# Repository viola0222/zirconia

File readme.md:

## 概要
___

「zirconia v.2.0」はマイクロマウスのチャンピオンが製作したオープンソースのマイクロマウスをnakagawaが改訂した版です。
 
詳しい説明は、[こちらのリンクの資料](https://docs.google.com/presentation/d/1BjXeR3dtw2jEZHByvPkCKbgB9d2WKhvbEWPhUpI-utg/edit?usp=sharing)を参照してください。

## 機能
___
 
各種インターフェースやセンサーの動作確認  

- マイコン各種機能(STM32F411)
- LED
- プッシュスイッチ
- モータ
- エンコーダ(MA730)
- IMU(ICM-42688-P)
- IRセンサ
  
機能の詳細についてはソフトマニュアルとサンプルコードのindex.hを参照して下さい。
 
## 動作環境
___
 
- 統合開発環境
    - STM32CubeIDE
    - Version :  1.15.0
    - URL : https://www.st.com/ja/development-tools/stm32cubeide.html
    - STM32CubeMX
    - Version :  6.10.0
    - URL : https://www.st.com/ja/development-tools/stm32cubemx.html    

- フラッシュライター
	- STM32CubeProgrammer
	- Version : 2.16.0
 	- URL : https://www.st.com/ja/development-tools/stm32cubeprog.html

※ Versionにはサンプルプログラムを開発したときのものを記載してあります。  
　　基本的には最新版をインストールすべきだと思いますが、  
　　サンプルプログラムが動かない等の不具合がありましたら参考にして下さい。

## 構成
___
 
- hardware
    - 回路図やガーバーデータ、部品リストなどハードウェアデータ
    - STEP 3D View https://a360.co/4cjsH3n
    
- software
    - CubeMXで自動生成したソフトと本サンプルプログラム
    - Incフォルダ内のIndex.hにサンプルプログラムの使い方が記載されています
    - Srcフォルダ内にmain.cなどのサンプルプログラムが入っています
- ハードマニュアル
    - ハードウェアの作り方や構成について記載されています
- ソフトマニュアル
    - サンプルプログラムの導入や使い方について記載されていますS
 
## その他
 ___

__本サンプルコードではマイクロマウスとして迷路を完走させることはできません。__  
本サンプルコードの目的は、製作したハードウェアの動作確認であり、その副産物として、マイクロマウスとして使いやすいデバイスドライバが書かれています。  
  
あくまでもzirconiaは動くハードウェアを用意しただけなので、ソフトウェアは自力で頑張れる人向けです。電子工作やプログラミングのガチ初心者にはオススメしません。  
電子工作や組み込みプログラム入門として、マイクロマウスを始める場合には(株)アールティより販売されている学習キット[Pi:Co Classic3.4 ESP32-S3](https://rt-net.jp/products/pico-classic3-esp32)や[Pi:Co V2](https://rt-net.jp/products/pico-v2)がオススメです。
 
## 作者
___
 
[Noriaki Nakagawa](https://github.com/noriakinakagawa)  
zirconia_sample is licensed under the Apache License, Version2.0

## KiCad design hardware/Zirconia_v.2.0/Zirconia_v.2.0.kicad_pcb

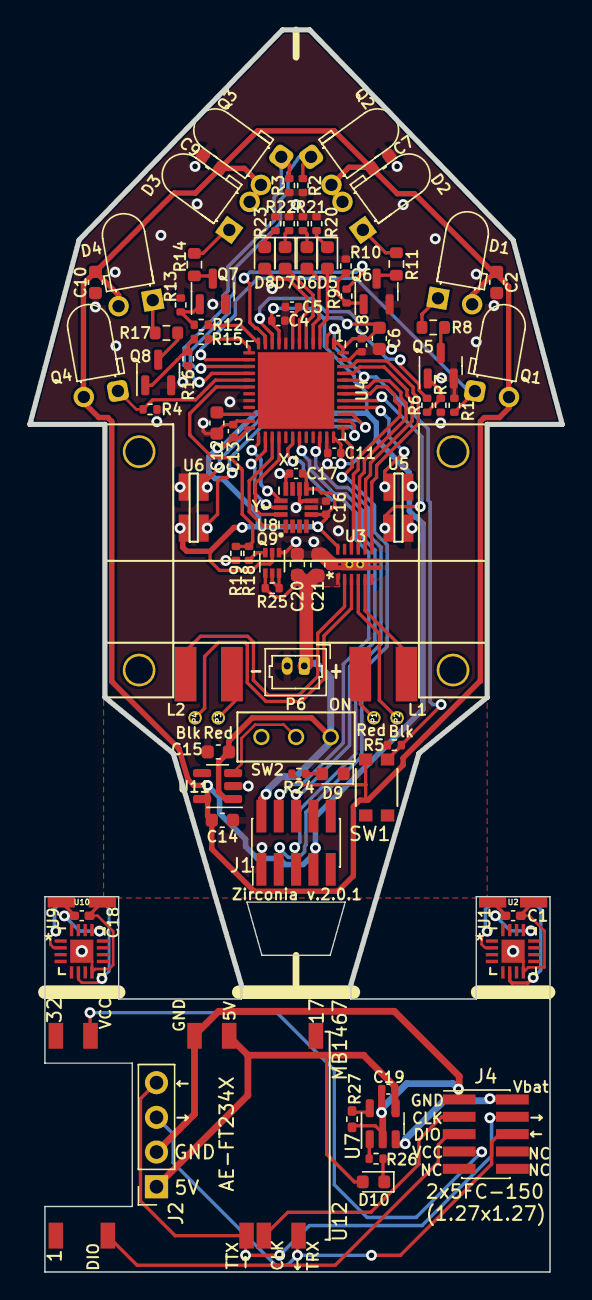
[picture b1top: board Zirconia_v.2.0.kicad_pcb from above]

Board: 2 copper layers, 39.0 x 90.9 mm, 91 parts (0 on the bottom side), 80 nets.

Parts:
C1, C18: 0.1u; C_0402_1005Metric_Pad0.74x0.62mm_HandSolder
C2, C6, C7, C9, C10, C12, C14, C15, C20, C21: 10u; C_0603_1608Metric
C4, C5, C8, C11, C13, C16: 0.1u; C_0402_1005Metric
C17: 10n; C_0402_1005Metric
C19: 4.7u; C_0402_1005Metric
D1, D3: OSI5FU3A11C
D2, D4: OSI5FU3A11C; OSI5FU3A11C_Reverse
D5: XL-1608UYC-06; LED_0603_1608Metric
D6, D10: XL-1608SURC-06; LED_0603_1608Metric
D7: XL-1608SYGC-06; LED_0603_1608Metric
D8, D9: XL-1608UBC-04; LED_0603_1608Metric
J1, J4: BD125-10-A-0305-0580-L-B; PinHeader_2x05_P1.27mm_Vertical_SMD
J2: Conn_01x04; PinSocket_1x04_P2.54mm_Vertical
L1, L2: 47uH; Inductor
Mot_mount: V; Mot_mount
P1, P3: Red; motor_pin
P2, P4: Blk; motor_pin
P6: PicoBlade_53047-0210; Molex_PicoBlade_53047-0210_1x02_P1.25mm_Vertical
Q1, Q2: LTR; Phototransistor_D3.0mm_Horizontal_O1.27mm_Z2.0mm_IRBlack
Q3, Q4: LTR; Phototransistor_D3.0mm_Horizontal_O1.27mm_Z2.0mm_IRBlack_Re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
Q5, Q6, Q7, Q8: IRLML6344; SOT-23
Q9: DMC2400UV-7; SOT-563
R1, R2, R3, R4, R6, R9, R12, R15, R20, R21, R23, R24, R26: 1k; R_0402_1005Metric
R5, R18, R19, R25: 10k; R_0402_1005Metric
R7, R10, R13, R16: 100k; R_0402_1005Metric
R8, R11, R14, R17: 10; R_0603_1608Metric
R22: 510; R_0402_1005Metric
R27: 10k; R_0402_1005Metric_Pad0.72x0.64mm_HandSolder
SW1: KMR211NG LFS; KMR2xxNG_LFS
SW2: SS12D01G4
U1, U9: MA302/MA730; MA302GQ-P
U2, U10: ENCODER_CONNECT_IC; ENC_CONN_VART
U3: DRV8836DSSR
U4: STM32F411CEU6/STM32F413CHU6; QFN-48-1EP_7x7mm_P0.5mm_EP5.6x5.6mm
U5, U6: ENCODER_CONNECT_PCB; ENC_CONN_FLAT
U7: MCP73831T-2ACI/OT; SOT-23-5
U8: ICM-42688-P; ICM-42688-P_handsoldering
U11: LP5907MFX-3.0; SOT-23-5
U12: STLINK-V3MOS; mod_stlink-v3m_mb1467

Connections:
+3V0: C2.1, C4.1, C6.1, C7.1, C8.1, C9.1, C10.1, C11.1, C13.1, C14.1, C16.1, C17.1, D1.2 (A), D2.2 (A), D3.2 (A), D4.2 (A), J1.7, Q1.2 (C), Q2.2 (C), Q3.2 (C), Q4.2 (C), Q9.2 (G), R24.2, SW1.2, U3.12 (NSLEEP), U4.1 (VBAT), U4.9 (VDDA/VREF+), U4.24 (VDD), U4.36 (VDD), U4.48 (VDD), U5.1 (VCC), U6.1 (VCC), U8.5 (VDDIO), U8.8 (VDD), U11.5 (OUT)
+BATT: C15.1, C20.1, C21.1, J1.2, P6.1, Q9.4 (S), R25.1, SW2.1 (A), U3.1 (VCC), U11.1 (IN)
GND: C2.2, C4.2, C5.2, C6.2, C7.2, C8.2, C9.2, C10.2, C11.2, C12.2, C13.2, C14.2, C15.2, C16.2, C17.2, C20.2, C21.2, D9.1 (K), J1.1, P6.2, Q5.2 (S), Q6.2 (S), Q7.2 (S), Q8.2 (S), Q9.1 (S), R1.2, R2.2, R3.2, R4.2, R5.2, R7.2, R10.2, R13.2, R16.2, R19.2, R20.1, R21.1, R22.1, R23.1, U3.6 (GND), U3.13 (EPAD), U4.8 (VSSA/VREF-), U4.20 (PB2/BOOT1), U4.23 (VSS), U4.35 (VSS), U4.47 (VSS), U5.2 (GND), U6.2 (GND), U8.6 (GND), U8.7 (RESV_7), U8.9 (INT2/FSYNC/CLKIN), U8.11 (RESV_11), U11.2 (GND)
unnamed: D1.1 (K), R8.1
unnamed: D2.1 (K), R11.1
unnamed: D3.1 (K), R14.1
unnamed: D4.1 (K), R17.1
unnamed: D5.2 (A), U4.3 (PC14/OSC32-IN)
unnamed: D5.1 (K), R20.2
unnamed: D6.2 (A), U4.4 (PC15/OSC32-OUT)
unnamed: D6.1 (K), R21.2
unnamed: D7.2 (A), U4.5 (PH0/OSC-IN)
unnamed: D7.1 (K), R22.2
unnamed: D8.2 (A), U4.6 (PH1/OSC-OUT)
unnamed: D8.1 (K), R23.2
unnamed: D9.2 (A), R24.1
unnamed: C19.1, D10.2 (A), J2.1, U7.4 (V_{DD}), U12.22 (5V_OPT)
unnamed: D10.1 (K), R26.2
unnamed: J1.3, U4.37 (PA14/SWCLK)
unnamed: J1.4, U4.30 (PA9/USART1TX)
unnamed: J1.5, U4.34 (PA13/SWDIO)
unnamed: J1.6, U4.31 (PA10/USRAT1RX)
unnamed: C19.2, J2.2, J4.1, R27.2, U7.2 (V_{SS}), U12.24 (GND)
unnamed: J2.3, J4.6, U12.15 (T_VCP_RX)
unnamed: J2.4, J4.4, U12.12 (T_VCP_TX)
unnamed: J4.2, U7.3 (V_{BAT})
unnamed: J4.3, U12.13 (T_JCLK/T_SWCLK)
unnamed: J4.5, U12.4 (T_JTMS/T_SWDIO)
unnamed: J4.7, U12.30 (T_VCC)
unnamed: L1.1, P1.1
unnamed: L2.1, P3.1
unnamed: Q1.1 (E), R1.1, U4.14 (PA4/ADC1-4)
unnamed: Q2.1 (E), R2.1, U4.15 (PA5/TIM2-1/SPI1SCK/ADC1-5)
unnamed: Q3.1 (E), R3.1, U4.16 (PA6/TIM3-1/SPI1MISO/ADC1-6)
unnamed: Q4.1 (E), R4.1, U4.17 (PA7/TIM3-2/SPI1MOSI/ADC1-7)
unnamed: Q5.3 (D), R8.2
unnamed: Q5.1 (G), R6.2, R7.1
unnamed: Q6.3 (D), R11.2
unnamed: Q6.1 (G), R9.2, R10.1
unnamed: Q7.3 (D), R14.2
unnamed: Q7.1 (G), R12.2, R13.1
unnamed: Q8.3 (D), R17.2
unnamed: Q8.1 (G), R15.2, R16.1
unnamed: Q9.5 (G), Q9.6 (D), R25.2
unnamed: Q9.3 (D), R18.1
unnamed: SW2.2 (B), U11.3 (EN)
unnamed: U1.2 (A), U2.3 (A)
unnamed: U1.6 (B), U2.4 (B)
unnamed: C1.1, U1.8 (GND), U1.17 (PAD), U2.2 (GND)
unnamed: C1.2, U1.13 (VDD), U2.1 (VCC)
unnamed: U3.10 (AIN1/APHASE), U4.42 (PB6/TIM4-1)
unnamed: U3.9 (AIN2/AENBL), U4.43 (PB7/TIM4-2)
unnamed: L2.2, U3.2 (AOUT1)
unnamed: P4.1, U3.3 (AOUT2)
unnamed: U3.8 (BIN1/BPHASE), U4.45 (PB8/TIM4-3)
unnamed: U3.7 (BIN2/BENBL), U4.46 (PB9/TIM4-4)
unnamed: P2.1, U3.4 (BOUT1)
unnamed: L1.2, U3.5 (BOUT2)
unnamed: R5.1, SW1.1, U4.2 (PC13), U4.44 (BOOT0)
unnamed: C5.1, U4.7 (NRST)
unnamed: R6.1, U4.10 (PA0/TIM2-1,5-1/ADC1-0)
unnamed: R9.1, U4.11 (PA1/TIM2-2,5-2/ADC1-1)
unnamed: R12.1, U4.12 (PA2/TIM2-3,5-3/ADC1-2)
unnamed: R15.1, U4.13 (PA3/TIM2-4,5-4/ADC1-3)
unnamed: U4.38 (PA15/TIM2-1), U6.3 (A)
unnamed: R18.2, R19.1, U4.18 (PB0/TIM3-3/ADC1-8)
unnamed: U4.39 (PB3/TIM2-2/SPI1SCK/SPI3SCK), U6.4 (B)
unnamed: U4.40 (PB4/TIM3-1/SPI1MISO/SPI3MISO), U5.3 (A)
unnamed: U4.41 (PB5/TIM3-2/SPI1MOSI/SPI3MOSI), U5.4 (B)
unnamed: U4.25 (PB12/SPI3SCK), U8.12 (AP_CS)
unnamed: U4.26 (PB13/SPI2SCK), U8.13 (AP_SCL/AP_SCLK)
unnamed: U4.27 (PB14/SPI2MISO), U8.1 (AP_SDO/AP_AD0)
unnamed: U4.28 (PB15/SPI2MOSI), U8.14 (AP_SDA/AP_SDIO/AP_SDI)
unnamed: C12.1, U4.22 (VCAP1)
unnamed: R27.1, U7.5 (PROG)
unnamed: R26.1, U7.1 (STAT)
unnamed: U9.2 (A), U10.3 (A)
unnamed: U9.6 (B), U10.4 (B)
unnamed: C18.1, U9.8 (GND), U9.17 (PAD), U10.2 (GND)
unnamed: C18.2, U9.13 (VDD), U10.1 (VCC)

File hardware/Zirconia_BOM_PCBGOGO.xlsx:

品名（Name） | 部品番号（Designator） | 個数（Quantity） | 値（Value） | パッケージ（Package） | 説明（Description） | 部品メーカー（Manufacturer） | 部品メーカーの型番（Manufacturer Part Number） | 代替可否だいたいかひ | Link
セラミックコンデンサ | C1,C4,C5,C8,C11,C13,C16,C17,C18,C19 | 10 | 0.1uF 16V | 表面実装1608mmひょうめんじっそう |  | Samsung | CL10B104KO8NNNC | 可か | https://www.digikey.jp/product-detail/ja/samsung-electro-mec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
セラミックコンデンサ | C2,C6,C7,C9,C10,C12,C14,C15 | 8 | 10uF 10V | 表面実装1608mmひょうめんじっそう |  | Samsung | CL10A106MP8NNNC | 可か | https://www.digikey.jp/product-detail/ja/samsung-electro-mec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
セラミックコンデンサ | C3 | 1 | 47uF 6.3V | 表面実装3216mmひょうめんじっそう |  | Samsung | CL31A476MQHNNWE | 可か | https://www.digikey.jp/product-detail/ja/samsung-electro-mec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
ＩＣ | U3 | 1 |  | 12-WFDFN | 向きがあるので、実装注意 (本ファイル別タブ「部品実装向き」参照)むじっそうちゅういほんべつﾌﾞﾋﾝｼﾞｯｿｳﾑさんしょう | Texas Instruments | DRV8836DSSR | 不可ふか | https://www.digikey.jp/product-detail/ja/texas-instruments/D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
インダクタ | L1,L2 | 2 | 47uH | 表面実装4.00mm x 4.00mmひょうめんじっそう |  | Vishay Dale | IFSC1515AHER470M01 | 不可ふか | https://www.digikey.jp/product-detail/ja/vishay-dale/IFSC151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
ＬＥＤ | D5 | 1 |  | 表面実装1608mmひょうめんじっそう | 向きがあるので、実装注意 (本ファイル別タブ「部品実装向き」参照)むじっそうちゅういほんべつﾌﾞﾋﾝｼﾞｯｿｳﾑさんしょう |  | HSMY-C190 | 可か | https://www.digikey.jp/product-detail/ja/broadcom-limited/HS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
ＬＥＤ | D6,D10 | 2 |  | 表面実装1608mmひょうめんじっそう | 向きがあるので、実装注意 (本ファイル別タブ「部品実装向き」参照)むじっそうちゅういほんべつﾌﾞﾋﾝｼﾞｯｿｳﾑさんしょう |  | HSMS-C190 | 可か | https://www.digikey.jp/product-detail/ja/broadcom-limited/HS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
ＬＥＤ | D7 | 1 |  | 表面実装1608mmひょうめんじっそう | 向きがあるので、実装注意 (本ファイル別タブ「部品実装向き」参照)むじっそうちゅういほんべつﾌﾞﾋﾝｼﾞｯｿｳﾑさんしょう |  | HSMG-C190 | 可か | https://www.digikey.jp/product-detail/ja/broadcom-limited/HS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
ＬＥＤ | D8,D9 | 2 |  | 表面実装1608mmひょうめんじっそう | 向きがあるので、実装注意 (本ファイル別タブ「部品実装向き」参照)むじっそうちゅういほんべつﾌﾞﾋﾝｼﾞｯｿｳﾑさんしょう |  | HSMR-C190 | 可か | https://www.digikey.jp/product-detail/ja/broadcom-limited/HS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
ＩＣ | U11 | 1 |  | SOT-23-5 |  | Texas Instruments | LP5907MFX-3.0/NOPB | 不可ふか | https://www.digikey.jp/product-detail/ja/texas-instruments/L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
ＩＣ | U7 | 1 |  | SOT-23-5 |  | Linear Technology/Analog Devices | LTC4054LES5-4.2#TRMPBF | 不可ふか | https://www.digikey.jp/product-detail/ja/linear-technology-a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
ＩＣ | U1, U9 | 2 |  | 16-VFQFN | 向きがあるので、実装注意 (本ファイル別タブ「部品実装向き」参照)むじっそうちゅういほんべつﾌﾞﾋﾝｼﾞｯｿｳﾑさんしょう | Monolithic Power Systems Inc. | MA300GQ-P | 不可ふか | https://www.digikey.jp/product-detail/ja/monolithic-power-sy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
ＭＯＳＦＥＴ | Q5,Q6,Q7,Q8 | 4 |  | SOT-23-3 |  | Infineon Technologies | IRLML6344TRPBF | 不可ふか | https://www.digikey.jp/product-detail/ja/infineon-technologi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
ＩＣ | U8 | 1 |  | 24-VFQFN | 向きがあるので、実装注意 (本ファイル別タブ「部品実装向き」参照)むじっそうちゅういほんべつﾌﾞﾋﾝｼﾞｯｿｳﾑさんしょう | TDK InvenSense | ICM-20648 | 不可ふか | https://www.digikey.jp/product-detail/ja/tdk-invensense/ICM-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
抵抗ていこう | R8,R11,R14,R17 | 4 | 10 Ohms | 表面実装1608mmひょうめんじっそう |  | Rohm Semiconductor | ESR03EZPF10R0 | 可か | https://www.digikey.jp/product-detail/ja/rohm-semiconductor/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
抵抗ていこう | R1,R2,R3,R4,R6,R9,R12,R15,R20,R21,R22,R23,R24,R25,R26,R27,R28 | 17 | 1 kOhms | 表面実装1608mmひょうめんじっそう |  | Susumu | RR0816P-102-D | 可か | https://www.digikey.jp/product-detail/ja/susumu/RR0816P-102-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
抵抗ていこう | R5,R18,R19 | 3 | 10 kOhms | 表面実装1608mmひょうめんじっそう |  | Susumu | RR0816P-103-D | 可か | https://www.digikey.jp/product-detail/ja/susumu/RR0816P-103-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
抵抗ていこう | R7,R10,R13,R16 | 4 | 100 kOhms | 表面実装1608mmひょうめんじっそう |  | Susumu | RR0816P-104-D | 可か | https://www.digikey.jp/product-detail/ja/susumu/RR0816P-104-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
ＩＣ | U4 | 1 |  | 48-UFQFN | 向きがあるので、実装注意 (本ファイル別タブ「部品実装向き」参照)むじっそうちゅういほんべつﾌﾞﾋﾝｼﾞｯｿｳﾑさんしょう | STMicroelectronics | STM32F413CHU6 | 不可ふか | https://www.digikey.jp/product-detail/ja/stmicroelectronics/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
スイッチ | SW1 | 1 |  |  |  | C&K | KMR211GLFS | 不可ふか | https://www.digikey.jp/product-detail/ja/c-k/KMR211GLFS/401-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

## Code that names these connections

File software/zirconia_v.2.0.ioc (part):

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Mcu.Name=STM32F411C(C-E)Ux
Mcu.Package=UFQFPN48
Mcu.UserName=STM32F411CEUx
PA0-WKUP.GPIOParameters=GPIO_Speed,GPIO_Label
PA0-WKUP.GPIO_Label=LED_FR
PA0-WKUP.GPIO_Speed=GPIO_SPEED_FREQ_VERY_HIGH
PA0-WKUP.Signal=GPIO_Output
PA1.GPIOParameters=GPIO_Speed,GPIO_Label
PA1.GPIO_Label=LED_SR
PA1.GPIO_Speed=GPIO_SPEED_FREQ_VERY_HIGH
PA1.Signal=GPIO_Output
PA10.Mode=Asynchronous
PA10.Signal=USART1_RX
PA13.Mode=Serial_Wire
PA13.Signal=SYS_JTMS-SWDIO
PA14.Mode=Serial_Wire
PA14.Signal=SYS_JTCK-SWCLK
PA15.Signal=S_TIM2_CH1_ETR
PA2.GPIOParameters=GPIO_Speed,GPIO_Label
PA2.GPIO_Label=LED_SL
PA2.GPIO_Speed=GPIO_SPEED_FREQ_VERY_HIGH
PA2.Signal=GPIO_Output
PA3.GPIOParameters=GPIO_Speed,GPIO_Label
PA3.GPIO_Label=LED_FL
PA3.GPIO_Speed=GPIO_SPEED_FREQ_VERY_HIGH
PA3.Signal=GPIO_Output
PA4.GPIOParameters=GPIO_Label
PA4.GPIO_Label=SEN_FR
PA4.Signal=ADCx_IN4
PA5.GPIOParameters=GPIO_Label
PA5.GPIO_Label=SEN_SR
PA5.Signal=ADCx_IN5
PA6.GPIOParameters=GPIO_Label
PA6.GPIO_Label=SEN_SL
PA6.Signal=ADCx_IN6
PA7.GPIOParameters=GPIO_Label
PA7.GPIO_Label=SEN_FL
PA7.Signal=ADCx_IN7
PA9.Mode=Asynchronous
PA9.Signal=USART1_TX
PB0.GPIOParameters=GPIO_Label
PB0.GPIO_Label=V_BAT
PB0.Signal=ADCx_IN8
PB12.GPIOParameters=GPIO_Speed,GPIO_Label
PB12.GPIO_Label=SPI2_CS
PB12.GPIO_Speed=GPIO_SPEED_FREQ_VERY_HIGH
PB12.Signal=GPIO_Output
PB13.Mode=Full_Duplex_Master
PB13.Signal=SPI2_SCK
PB14.Mode=Full_Duplex_Master
PB14.Signal=SPI2_MISO
PB15.Mode=Full_Duplex_Master
PB15.Signal=SPI2_MOSI
PB3.Signal=S_TIM2_CH2
PB4.Signal=S_TIM3_CH1
PB5.Signal=S_TIM3_CH2
PB6.GPIOParameters=GPIO_Speed,GPIO_Label
PB6.GPIO_Label=MOT_RF
PB6.GPIO_Speed=GPIO_SPEED_FREQ_VERY_HIGH
PB6.Signal=S_TIM4_CH1
PB7.GPIOParameters=GPIO_Speed,GPIO_Label
PB7.GPIO_Label=MOT_RR
PB7.GPIO_Speed=GPIO_SPEED_FREQ_VERY_HIGH
PB7.Signal=S_TIM4_CH2
PB8.GPIOParameters=GPIO_Speed,GPIO_Label
PB8.GPIO_Label=MOT_LF
PB8.GPIO_Speed=GPIO_SPEED_FREQ_VERY_HIGH
PB8.Signal=S_TIM4_CH3
PB9.GPIOParameters=GPIO_Speed,GPIO_Label
PB9.GPIO_Label=MOT_LR
PB9.GPIO_Speed=GPIO_SPEED_FREQ_VERY_HIGH
PB9.Signal=S_TIM4_CH4
PC13-ANTI_TAMP.GPIOParameters=GPIO_Label
PC13-ANTI_TAMP.GPIO_Label=SWITCH
PC13-ANTI_TAMP.Signal=GPIO_Input
PC14-OSC32_IN.GPIOParameters=GPIO_Label
PC14-OSC32_IN.GPIO_Label=LED_YELLOW
PC14-OSC32_IN.Signal=GPIO_Output
PC15-OSC32_OUT.GPIOParameters=GPIO_Label
PC15-OSC32_OUT.GPIO_Label=LED_RED
PC15-OSC32_OUT.Signal=GPIO_Output
PH0\ -\ OSC_IN.GPIOParameters=GPIO_Label
PH0\ -\ OSC_IN.GPIO_Label=LED_GREEN
PH0\ -\ OSC_IN.Signal=GPIO_Output
PH1\ -\ OSC_OUT.GPIOParameters=GPIO_Label
PH1\ -\ OSC_OUT.GPIO_Label=LED_BLUE
PH1\ -\ OSC_OUT.Signal=GPIO_Output
RCC.HSE_VALUE=25000000
RCC.SYSCLKFreq_VALUE=96000000
RCC.SYSCLKSource=RCC_SYSCLKSOURCE_PLLCLK
board=custom

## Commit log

2019-05-11 First
2020-04-13 readmeの追加と細かいバグの修正
2020-04-13 readmeの追加と細かい修正
2020-04-13 文字化け対策
2020-04-19 CubeIDE対応
2020-04-19 マニュアル更新
2022-04-04 ライセンスの追加
2022-07-31 フォルダ構成の変更
2022-07-31 開発環境のバージョンアップ
2022-07-31 DMA割込みの優先順位変更
2022-07-31 割込処理割合のオーバーフロー対策
2022-07-31 フラッシュ機能の実装
2022-07-31 readmeの修正
2023-08-14 IMUが1度しか更新されないバグの修正
2023-08-14 光センサ位置の表示修正
2023-08-17 最適化対策とリファクタリング
2024-06-02 update bom
2024-06-06 add AE-FT234X
2024-07-31 JLCPCBパーツ反映
2024-10-08 WIP: 宴会芸
2024-10-09 Linux + arm-none-eabi でビルドできるように
2024-10-22 WindowsでMakeを使ってコンパイルが通るようになった
